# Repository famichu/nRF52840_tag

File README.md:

# nRF52840 tag

## What's this?

This is a development board works with coin batteries based on Adafruit Feather nRF52840 Express. This board works on all bootloaders of Adafruit Feather nRF52840 Express.

## Features

- Works with coin battery(CR2032)
- Extra battery(PH connector) support(Not suport charging)
- USB Type-C(USB 2.0)
- Warking same as Adafruit Feather nRF52840 Express(CircuitPython etc)
    - Programmable Full color LED(NeoPIXEL)
    - 1 usable push switch in program
    - 16MBit Flash memory

## How to use

1. Connect j-link and this board via SWD vias back side of this board.
2. Burn a bootloader you want to use with nrfjprog command.
    (For more detail, read "Burninng new Bootloader" on [adafruit's github](https://github.com/adafruit/Adafruit_nRF52_Arduino)

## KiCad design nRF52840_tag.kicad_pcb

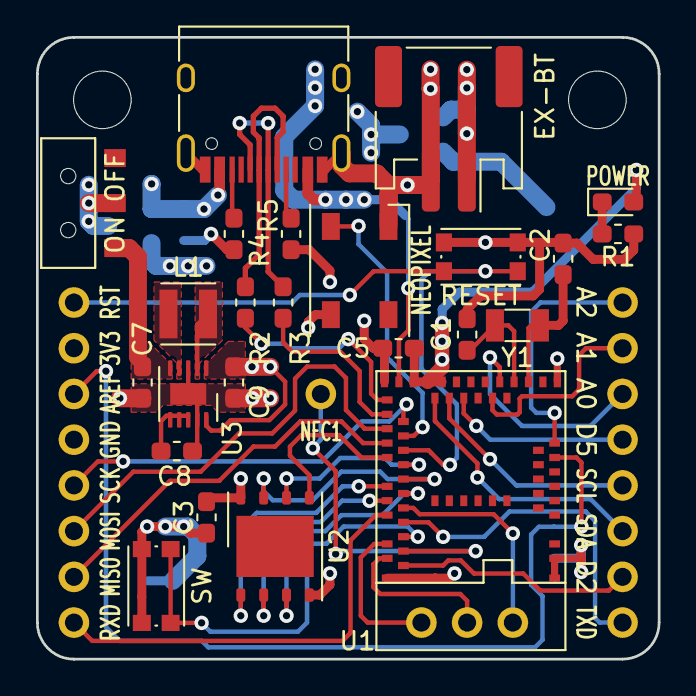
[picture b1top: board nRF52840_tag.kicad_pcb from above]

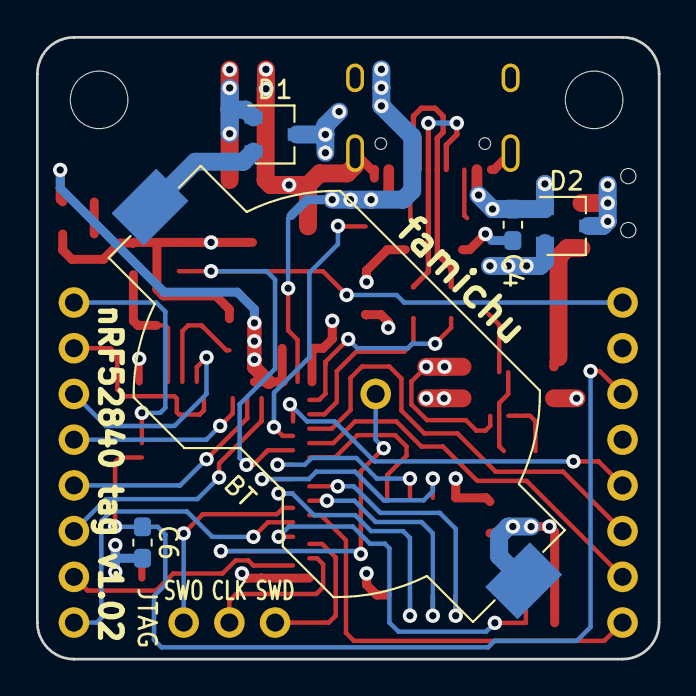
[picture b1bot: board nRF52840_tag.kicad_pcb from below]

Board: 4 copper layers, 34.5 x 34.5 mm, 35 parts (6 on the bottom side), 46 nets.

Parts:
BT: Battery_Cell; BatteryHolder_Keystone_1058_1x2032
C1, C2: 22pF; C_0603_1608Metric_Pad1.05x0.95mm_HandSolder
C3, C4, C7: 10uF; C_0603_1608Metric_Pad1.05x0.95mm_HandSolder
C5, C6, C8: 0.1uF; C_0603_1608Metric_Pad1.05x0.95mm_HandSolder
C9: 22uF; C_0603_1608Metric_Pad1.05x0.95mm_HandSolder
D1, D2: RB411D; SOT-23W
EX-BT: Conn_01x02; JST_PH_S2B-PH-SM4-TB_1x02-1MP_P2.00mm_Horizontal
H1, H2: MountingHole; MountingHole_3.2mm_M3
J1, J3: Conn_01x08; PinHeader_1x08_P2.54mm_Vertical
JTAG: Conn_01x03_Female; PinSocket_1x03_P2.54mm_Vertical
L1: L; L_Neosid_SMS-ME3015
NEOPIXEL: WS2812B; LED_WS2812B_PLCC4_5.0x5.0mm_P3.2mm
NFC1: Conn_01x01_Female; PinHeader_1x01_P2.54mm_Vertical
ON OFF: SW_SPDT; Slide_Switch_AYZ
P1: USB_C_Plug_USB2.0; USB_C_Receptacle_HRO_TYPE-C-31-M-12
POWER: POW; LED_0603_1608Metric_Pad1.05x0.95mm_HandSolder
R1: 1k; R_0603_1608Metric_Pad1.05x0.95mm_HandSolder
R2, R3: 22; R_0603_1608Metric_Pad1.05x0.95mm_HandSolder
R4, R5: 5.1k; R_0603_1608Metric_Pad1.05x0.95mm_HandSolder
RESET: SW_Push; SW_Push_1P1T_NO_CK_KMR2
SW: SW_Push; SW_Push_1P1T_NO_CK_KMR2
U1: MDBT50Q; MDBT50Q-1MV2
U2: GD25D10CT; WSON-8-1EP_6x5mm_P1.27mm_EP3.4x4.3mm
U3: TPS63031DSK; VSON-10-1EP_3x3mm_P0.5mm_EP1.2x2mm
Y1: 32.768; Crystal_SMD_3215-2Pin_3.2x1.5mm

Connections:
+3V3: C3.1, C5.1, C9.1, J1.2, NEOPIXEL.1, POWER.2, U1.28, U1.30, U1.31, U2.8, U3.1, U3.10
+BATT: D1.3, D2.2
/A0: J3.6, U1.20
/A1: J3.7, U1.21
/A2: J3.8, U1.14
/AREF: C6.1, J1.3, U1.12
/D2: J3.2, U1.54
/D5: J3.5, U1.25
/MISO: J1.7, U1.39
/MOSI: J1.6, U1.37
/NEOPIX: NEOPIXEL.4, U1.38
/NFC1: NFC1.1, U1.52
/QSPI_CS: U1.44, U2.1
/QSPI_DATA0: U1.41, U2.5
/QSPI_DATA1: U1.46, U2.2
/QSPI_DATA2: U1.45, U2.3
/QSPI_DATA3: U1.43, U2.7
/QSPI_SCK: U1.42, U2.6
/RESET: J1.1, RESET.2, U1.40
/RXD: J1.8, U1.48
/SCK: J1.5, U1.36
/SCL: J3.4, U1.27
/SDA: J3.3, U1.29
/SWCLK: JTAG.2, U1.53
/SWDIO: JTAG.3, U1.51
/SWITCH: SW.2, U1.50
/SWO: JTAG.1, U1.47
/TXD: J3.1, U1.49
/USBD+: R3.1, U1.35
/USBD-: R2.1, U1.34
GND: BT.2, C1.2, C2.2, C3.2, C4.2, C5.2, C6.2, C7.2, C8.2, C9.2, EX-BT.2, J1.4, NEOPIXEL.3, P1.A1, P1.A12, P1.B1, P1.B12, P1.S1, R1.1, R4.2, R5.2, RESET.1, SW.1, U1.1, U1.2, U1.15, U1.33, U1.55, U2.4, U3.3, U3.9, U3.11
unnamed: BT.1, D1.2
unnamed: C1.1, U1.18, Y1.1
unnamed: C2.1, U1.17, Y1.2
unnamed: C7.1, ON OFF.3, U3.5
unnamed: C8.1, U3.6, U3.7, U3.8
unnamed: D1.1, EX-BT.1
unnamed: D2.3, ON OFF.2
unnamed: L1.1, U3.4
unnamed: L1.2, U3.2
unnamed: P1.A5, R5.1
unnamed: P1.A6, P1.B6, R3.2
unnamed: P1.A7, P1.B7, R2.2
unnamed: P1.B5, R4.1
unnamed: POWER.1, R1.2
VBUS: C4.1, D2.1, P1.A4, P1.A9, P1.B4, P1.B9, U1.32

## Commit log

2021-06-21 Create LICENSE
